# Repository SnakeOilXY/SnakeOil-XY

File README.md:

# SnakeOil XY

Fully open source configurable high speed CoreXY 3D printer. Inspired by [HevORT](https://miragec79.github.io/HevORT/), [Voron](https://vorondesign.com/), [Annex Engineering](https://github.com/Annex-Engineering) and [EVA2](https://main.eva-3d.page/) design.

- Does not require any custom-machined parts or custom-cut panels.
- Can be selected one of the follwing kinematics.
    - Standard : Traditional corexy kinematic.
    - 4PR : High-performance machine with automatic squaring gantry capacity. This configuration uses custom [Extended CoreXY kinematic](https://github.com/SnakeOilXY/klipper-extended-corexy-kinematic) (Mixed cartesian and corexy).
    - IDEX : Hybrid corexy IDEX.
- CoreXY, IDEX, and Extended-CoreXY kinematics.
- Designed to last, parts under stress are embedded with long bolts to handle the load.
- And our industry-leading SnakeOil technology :3 

## Beta 3 release (2023-01-28)

- Add [IDEX variant](./BETA3_IDEX_Release_STL)(by Charles)
- Add [4PR variant](./BETA3_4PR_Release_STL) with new [Extended CoreXY kinematic](https://github.com/SnakeOilXY/klipper-extended-corexy-kinematic)
- Add klicky probe support(by Charles)
- New bed coupling kinematic using silicon spacers
- Add side-blower aux fan module
- Add EBB can toolhead board support
- Remove outdated components
- Merge toolhead design(1515 and 2020 gantry now use the same toolhead front/back/bottom design) and some small improvements on geometry

## Features

<table>
    <thead>
        <tr>
            <th>Feature</th>
            <th>Credit/Inspiration by/Description</th>
        </tr>
    </thead>
    <tbody>
        <tr>
            <td>Selectable kinematic : CoreXY, Hibryd-CoreXY </td>
            <td>Added on beta3 release</td>
        </tr>
        <tr>
            <td>Selectable single or dual toolhead </td>
            <td>Added on beta3 release</td>
        </tr>
        <tr>
            <td>3 Point auto bed tramming</td>
            <td>HevORT, Wobble ring</td>
        </tr>
        <tr>
            <td>Belted Z</td>
            <td>Lulz bot, Voron</td>
        </tr>
        <tr>
            <td>Din mounter</td>
            <td>Voron</td>
        </tr>
        <tr>
            <td>Cross belt corexy belt path</td>
            <td>HevORT</td>
        </tr>
        <tr>
            <td>Eva compatible toolhead</td>
            <td>EVA</td>
        </tr>
        <tr>
            <td>Filament spoll in side chamber</td>
            <td>-</td>
        </tr>
        <tr>
            <td>Quick release panels</td>
            <td>Added on beta2 release</td>
        </tr>
        <tr>
            <td>Built-in chamber air filter</td>
            <td>Added on beta1 release</td>
        </tr>
        <tr>
            <td>Auto build sheet detect and profile loader</td>
            <td>Work in progress</td>
        </tr>
        <tr>
            <td>AIO filament runout + jam detector + width sensor</td>
            <td>Work in progress</td>
        </tr>
        <tr>
            <td>Modular sensor add-on system</td>
            <td>Work in progress</td>
        </tr>
        <tr>
            <td>Probe(bed mesh) on print area only</td>
            <td>Added on beta2 using klipper macro</td>
        </tr>
        <tr>
            <td>Screwless belt mounter</td>
            <td>VzBot</td>
        </tr>
        <tr>
            <td>Bed fan</td>
            <td>Qholia</td>
        </tr>
    </tbody>
</table>

## Input shaper test result (beta2 1515 gantry with Sherpa mini extruder)

## Layer pitch measure (beta2 1515 gantry with Sherpa mini extruder)

- Measure result provided by [株式会社グーテンベルク](https://gutenberg.co.jp/)
- PLA, 0.4mm nozzle, sliced with Cura 4.12.1 using "CoreXY FAST" profile.

## Demo videos

<table>
    <thead>
        <tr>
            <th></th>
            <th align="center">Bed coupling</th>
            <th align="center">SpeedBoatRace</th>
            <th align="center">Slow benchy</th>
        </tr>
    </thead>
    <tbody>
        <tr>
            <td>Video</td>
            <td align="center"></td>
            <td align="center"></td>
            <td align="center"></td>
        </tr>
        <tr>
            <td>Hardware version</td>
            <td align="center">beta1</td>
            <td align="center">beta2</td>
            <td align="center">beta2</td>
        </tr>
    </tbody>
</table>

## BOM

## **_SnakeOil-XY currently has 2 versions_**

<code>Both machines are practicaly identical, only difference is the build volume. </code>

### 180x180x180mm build volume (Standard)

- [180<sup>3</sup>mm BOM](./Doc/BOM/bom-180.md)

### 250x240x230mm build volume (Large)

- [250<sup>3</sup>mm BOM](./Doc/BOM/bom-250.md)

## Manual

[>>> Click here <<<](./Doc/Manual/README.md)

## Firmware

[>>> Click here <<<](./Firmware/README.md)

## Copyright Notice

- [Sherpa mini extruder](https://github.com/Annex-Engineering/Sherpa_Mini-Extruder) is an original work of [Annex Engineering](https://github.com/Annex-Engineering), modified parts using their source code/design files are re-released under [ANNEX Engineering License](https://github.com/Annex-Engineering/ANNEX-Engineering-License-Agreement/blob/main/LICENSE.md).
- [EVA2](https://github.com/EVA-3D/eva-main) is an original work of [EVA-3D](https://github.com/EVA-3D), modified parts using their source code/design files are re-released under [GNU General Public License v3.0](https://github.com/EVA-3D/eva-main/blob/main/LICENSE)
- This printer design(SnakeOil XY), it's document and software are released under [GNU General Public License v3.0](https://github.com/ChipCE/SnakeOil-XY/blob/master/LICENSE)

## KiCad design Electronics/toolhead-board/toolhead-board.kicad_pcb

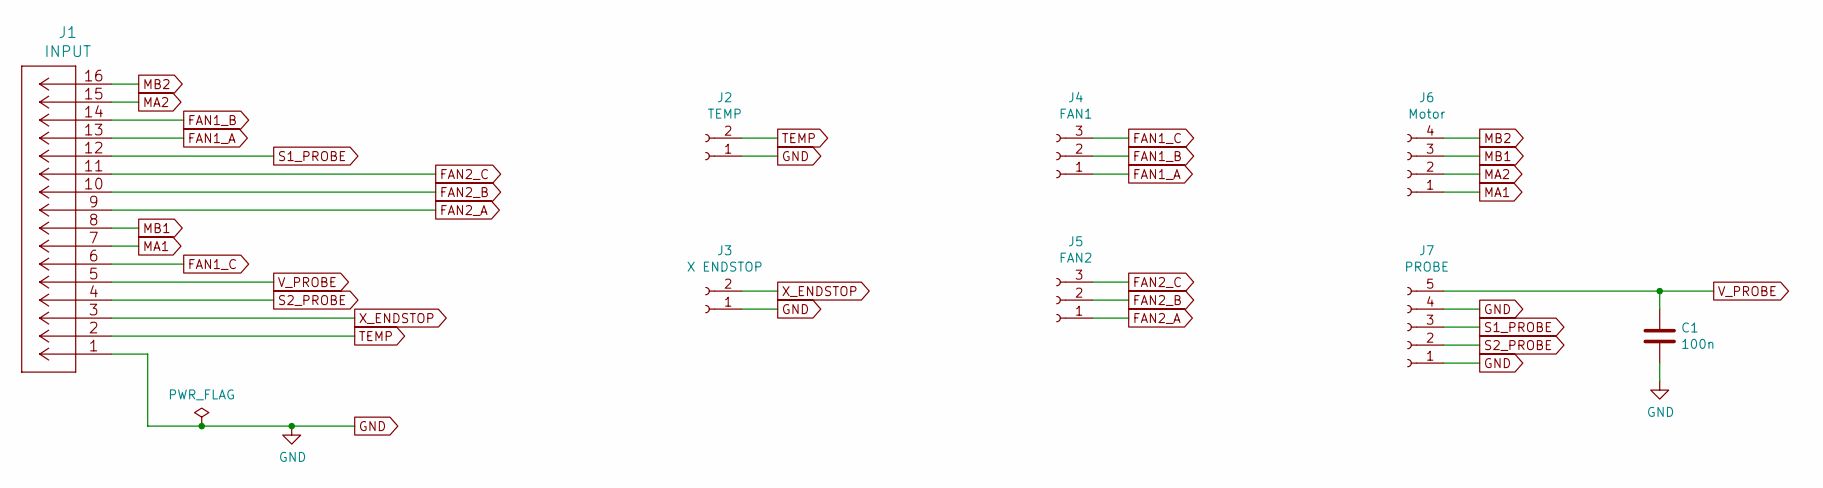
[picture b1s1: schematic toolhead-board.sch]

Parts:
C1: 100n; C_0805_2012Metric_Pad1.15x1.40mm_HandSolder
J1: INPUT; microfit-16
J2: TEMP; JST_XH_B02B-XH-A_1x02_P2.50mm_Vertical
J3: X ENDSTOP; JST_XH_B02B-XH-A_1x02_P2.50mm_Vertical
J4: FAN1; JST_XH_B03B-XH-A_1x03_P2.50mm_Vertical
J5: FAN2; JST_XH_B03B-XH-A_1x03_P2.50mm_Vertical
J6: Motor; JST_XH_B04B-XH-A_1x04_P2.50mm_Vertical
J7: PROBE; JST_XH_B05B-XH-A_1x05_P2.50mm_Vertical

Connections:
FAN1_A: J1.13, J4.1
FAN1_B: J1.14, J4.2
FAN1_C: J1.6, J4.3
FAN2_A: J1.9, J5.1
FAN2_B: J1.10, J5.2
FAN2_C: J1.11, J5.3
GND: C1.2, J1.1, J2.1, J3.1, J7.1, J7.4
MA1: J1.7, J6.1
MA2: J1.15, J6.2
MB1: J1.8, J6.3
MB2: J1.16, J6.4
S1_PROBE: J1.12, J7.3
S2_PROBE: J1.4, J7.2
TEMP: J1.2, J2.2
V_PROBE: C1.1, J1.5, J7.5
X_ENDSTOP: J1.3, J3.2

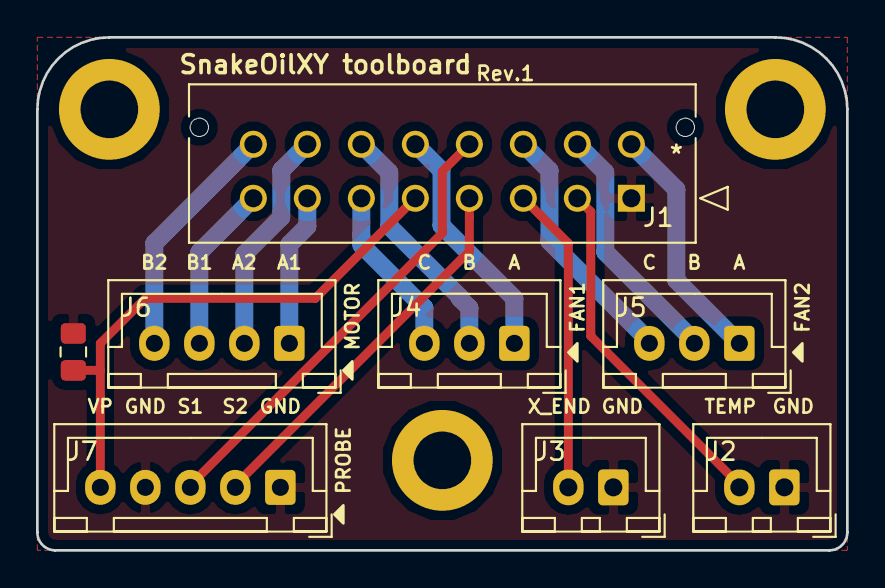
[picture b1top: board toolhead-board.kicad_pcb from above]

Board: 2 copper layers, 45.0 x 28.5 mm, 8 parts (0 on the bottom side), 16 nets.

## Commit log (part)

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2021-06-24 update CAD
2021-06-26 update CAD, BOM
2021-06-27 update bom
2021-06-27 Create LICENSE
2021-06-28 sync
2021-06-29 update BOM, change files layout
2021-06-29 update door assembly, BOM
2021-06-29 added neopixel mount
2021-06-30 update CAD,BOM, bed drawing
2021-07-01 update doc
2021-07-02 revert 190mm bed drawing
2021-07-05 update Y-carrier, BOM
2021-07-08 update BOM, front idler
2021-07-10 update Z motor mount, z block mount
2021-07-11 added aligner
2021-07-11 update BOM(m6x15), CAD
2021-07-11 added logo
2021-07-12 added rail-aligner tool
2021-07-13 update AB motor mounts
2021-07-15 update toolhead parts
2021-07-17 fixed z-motor-cap
2021-07-18 update bottom-panel, fixed z idler housing
2021-07-18 fixed y carrier
2021-07-18 fixed corupted file
2021-07-19 update z belt mounter
2021-07-20 fixed x-endstop
2021-07-21 update y carrier, din mount
2021-07-21 added belt path
2021-07-21 fix z-idler
2021-07-22 fixed motor cover plate
2021-07-24 update bed-assembly,added mgn12c-z-mount
2021-07-25 update Z-idler
2021-07-26 update bottom panel, z motor cover
2021-07-28 update neopixel mount
2021-08-02 update bottom plate
2021-08-04 update z idler mount
2021-08-10 update panel mount
2021-08-12 update pane & cable mounter
2021-08-13 added AD socket mounter
2021-08-16 added cable mounter
2021-08-20 update Z rail mounts, BOM
2021-08-21 added hepa+carbon filter
2021-08-22 update air filter, added spool holder
2021-08-23 update spool holder
2021-08-31 added STEP
2021-08-31 added STLs
2021-09-01 added missing STL, update Readme.md
2021-09-05 add top lid, updat BOM
2021-09-06 added 250x240x230 frame bom
2021-09-08 update front door
2021-09-15 update drawing, BOM
2021-09-25 update link for camera
2021-10-02 fixed bom
2021-10-02 fixed bom - again
2021-10-05 added document for EVA2
2021-10-07 update STEP, front panel mount
2021-10-08 update CAD, new STL
2021-10-10 added 2gt-strap
2021-10-10 2gt strap- smaller
2021-10-13 added compact toolhead
2021-10-14 update compact toolhead
2021-10-15 fixed extrusion length of 250 frame
2021-10-20 update gantry
2021-10-24 Z rail block with limiter by default
2021-10-27 Beta 2 release
2021-10-27 update step files
2021-10-28 update BOM, added option for threaded ball bed coupler
2021-10-30 update BOM for threaded ball coupler
2021-11-01 added din cable mounter stl
2021-11-01 fixed links
2021-11-01 update BOM links
2021-11-03 added missing stls
2021-11-05 update 250 BOM
2021-11-06 update panel mount, screw bom
2021-11-07 added missing stl
2021-11-07 added 250 frame step
2021-11-09 added 5x65 shaft drawing
2021-11-09 added tmp 250 bed drawing
2021-11-09 update drawing
2021-11-10 update heater drawing
2021-11-10 added parts for makerbeamxl
2021-11-11 - Update silicon heater drawing - Add printable 80t pulley by Charles - sync wip assembly
2021-11-11 Air filter assembly in A4
2021-11-11 Updated the BOM with links for every item. Added hotends, boards and more.
2021-11-11 Added logos, fixed BOM redirects.
2021-11-11 README
2021-11-11 fixed drawing
2021-11-13 updated heater drawing description
2021-11-13 update panel size for 250 machine
2021-11-13 update assembly
2021-11-13 fixed broken link
2021-11-13 fixed assembly
2021-11-16 update assembly, sherpa mini mod STLs
2021-11-17 update generateBom.py - identify printed parts by printed_parts_colors - refactored to be more pythonic - now opens a GUI window (otherwise we cannot get color) - can be run from the console OR as a 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
2021-11-18 fixed parts name in assembly
2021-11-19 added 2010 gantry
2021-11-23 update BOM, remove M10 bolts
2021-11-27 added bottom panel for 250 machine
2021-11-30 update 250 bottom panel
2021-11-30 update 180 panel
2021-11-30 update bottom panel
2021-11-30 fix STLs orientation
2021-12-01 update 1515 bed cable mounter, added cherrymx button cap template
2021-12-04 updated 2010 gantry
2021-12-04 update 2010 assembly
2021-12-04 added glass bed assembly
2021-12-05 remov M4x12 from BOM
2021-12-12 update Z motor cover
2021-12-12 update stl
2021-12-12 fixed stl orientation
2021-12-12 update Z gear box STLs, CAD
2021-12-13 update carbon fiber gantry frawing
2021-12-14 Z axis gear box : Improvement cable management
2021-12-14 update stl orientation
2021-12-14 added big-boi bed concept
2021-12-19 added testing files
2021-12-20 added dual 5015 toolhead
2021-12-21 added support for eva 2.4
2021-12-21 added compact serpa mini mount for nova
2021-12-21 update eva2 doc
2021-12-22 pulled new ducts from eva2
2021-12-23 add lighter variant of extruder front plate
2021-12-24 update toolhead
2021-12-25 hollow out unned parts of toolhead back plate
2021-12-30 uppdate pre-flight check document
2021-12-30 fixed typo
2021-12-30 fixed type
2021-12-31 update documents, add STL for extrusion drilling tool
2022-01-01 fixed gasket and din mount
2022-01-03 remove old parts from BOM
2022-01-03 update BOM, add patch for Z rail block mount
2022-01-03 fix Z block mount
2022-01-04 update CAD requirement
2022-01-04 Fix various typos
    Found via `codespell -q 3`
2022-01-05 Added another correction
2022-01-05 Fix typo in source
2022-01-07 update din mounters
2022-01-08 added counter weight
2022-01-10 fixed panel mount
2022-01-12 update BOM, assembly
2022-01-14 update toolhead back plate
2022-01-20 update bed fan mounter
2022-01-21 update config
2022-01-22 fix 120mm fan mounter
2022-01-23 fixed stl
2022-01-24 add panel drawings
2022-01-25 Split the BOM for 180 and 250mm
2022-01-25 Update preflight-check.md
    add FILAMENT_TYPE variable for prusa slicer
2022-01-26 ipdate preflight check
2022-01-26 Update bom-180.md
    update qty of e3d bowden collet for filament arm
2022-01-28 update ptfe tube mount, camera mount
2022-01-30 fixed md table
2022-02-01 Added Tensioning Idlers in Mod folder. Reorganized the folder structure in the STLs section. Combined the tools folder and tools folder in stls folder. Added recommended to the default optoins when a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
2022-02-02 update stl folder structure
2022-02-02 html tables
    I converted the tables from .md to .html, removed the "BOM-README" and moved its information to the main readme
2022-02-02 update neopixel mount, reinforce Z motor mount
2022-02-02 added bottom panel mount with offset
2022-02-02 fixed STLs orientation
2022-02-02 BOM tables in html
    I converted the tables in the BOM from md style to html style, relocated a few things, and added a "tutorial" for brackets
2022-02-06 added panel drawings
2022-02-12 Simplified fasteners list
2022-02-17 Organizing the BOM
2022-02-19 added missing cutout on Z motor mount
2022-03-05 added CF gantry mounter
2022-03-09 added counter-weight
2022-03-22 add old 12864
2022-03-29 added Panasonic probe mount
2022-04-07 added toolhead pcb files
2022-05-11 added bottom din mounter for 250 machine
2022-05-11 update freq calc
2022-05-22 update resonance tuning guide
2022-05-22 typo
2022-05-22 Fixed english mistakes in the reasonance tuning guide
2022-05-22 Create engineer1901mod
2022-05-22 Create 250-carbon-fiber-tube-drawing-new
2022-06-02 update advance resonance tuning guide
2022-06-02 update shaper tuning guide
2022-06-02 remove escape chars
2022-07-30 update back panel gasket
2022-08-24 update idex plates
2022-08-26 cleanup old files, merged toolhead design
2022-08-29 update dead links
2022-09-20 added idex belt mounter
2022-10-14 init beta3
2022-10-25 removed M5 thread insert from idex motor mount
2022-10-27 update e_corexy doc
2022-11-01 update can board mounter
2022-11-01 added stl for can mounter
2022-11-18 Idex Stls and in progress BOM
2022-11-18 Added CAD
2022-11-19 change folder name to standard_release
2022-11-20 addition of the bed-z-probe
2022-11-20 addition of z-bed-enstop in cad
2022-11-20 Added Strain Relief for toolheads
2022-12-01 update can spacer
2022-12-01 update 4PR bom
2022-12-10 change kinematic link
2022-12-12 update panel clip
2022-12-18 added silicon z arm mount
2022-12-29 added aux fan
2023-01-10 added 120mm fan mount for 2020-250 bed frame
2023-01-10 update aux fan mounter
2023-01-13 add inlet with switch mounter
2023-01-14 add adxl345 mount
2023-01-27 update file layout
2023-01-27 update 250 machine heater size
2023-01-29 update mob for aux fan
2023-02-05 update neopixel endcap
2023-02-12 update 4PR Y carrier
2023-02-13 move 2020 y carrier assembly
2023-02-26 add U2C din mounter
2023-03-18 add nevermore micro mod
2023-04-16 Squashed commit of the following:
    - add code for adding part colors to STL file names
    - rename ambiguous CAD components and STL files to match
2023-04-16 code splitting
2023-04-16 improve logging messages
2023-04-16 add color categories to stl file names
2023-04-18 add top plate for 2020 sensorless homing
2023-04-30 add SS180 frame drawing
2023-04-30 update frame drawing
2023-05-01 update 4PR readme
2023-06-14 add z endstop, FR4 y carrier
2023-07-06 update FR4 mounting plate
2023-11-27 add new front idler
2023-11-28 add new front-idler and toolhead mounter
2023-11-28 add new front-idler
2023-12-27 update idex parts
2023-12-28 update IDEX bottom and back plate(use instert instead of hex nut)
2024-01-18 restore old bed fan mount cad
2024-02-01 add filament arm for trianglelab collet
2024-02-18 update sample config
2024-05-04 add 4PR+4FR reinforce STLs
2025-02-01 add rail stopper
2025-02-05 Update bom-IDEX.md
    No longer available.
2025-02-05 Update bom-250.md, mellow kit no longer available.
2025-02-05 Update bom-180.md, mellow kit no longer available.
2025-10-22 new 4PR Y-carriers

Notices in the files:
parts and their libraries:
Copyright 2021 Accelerated Designs. All rights reserved.
